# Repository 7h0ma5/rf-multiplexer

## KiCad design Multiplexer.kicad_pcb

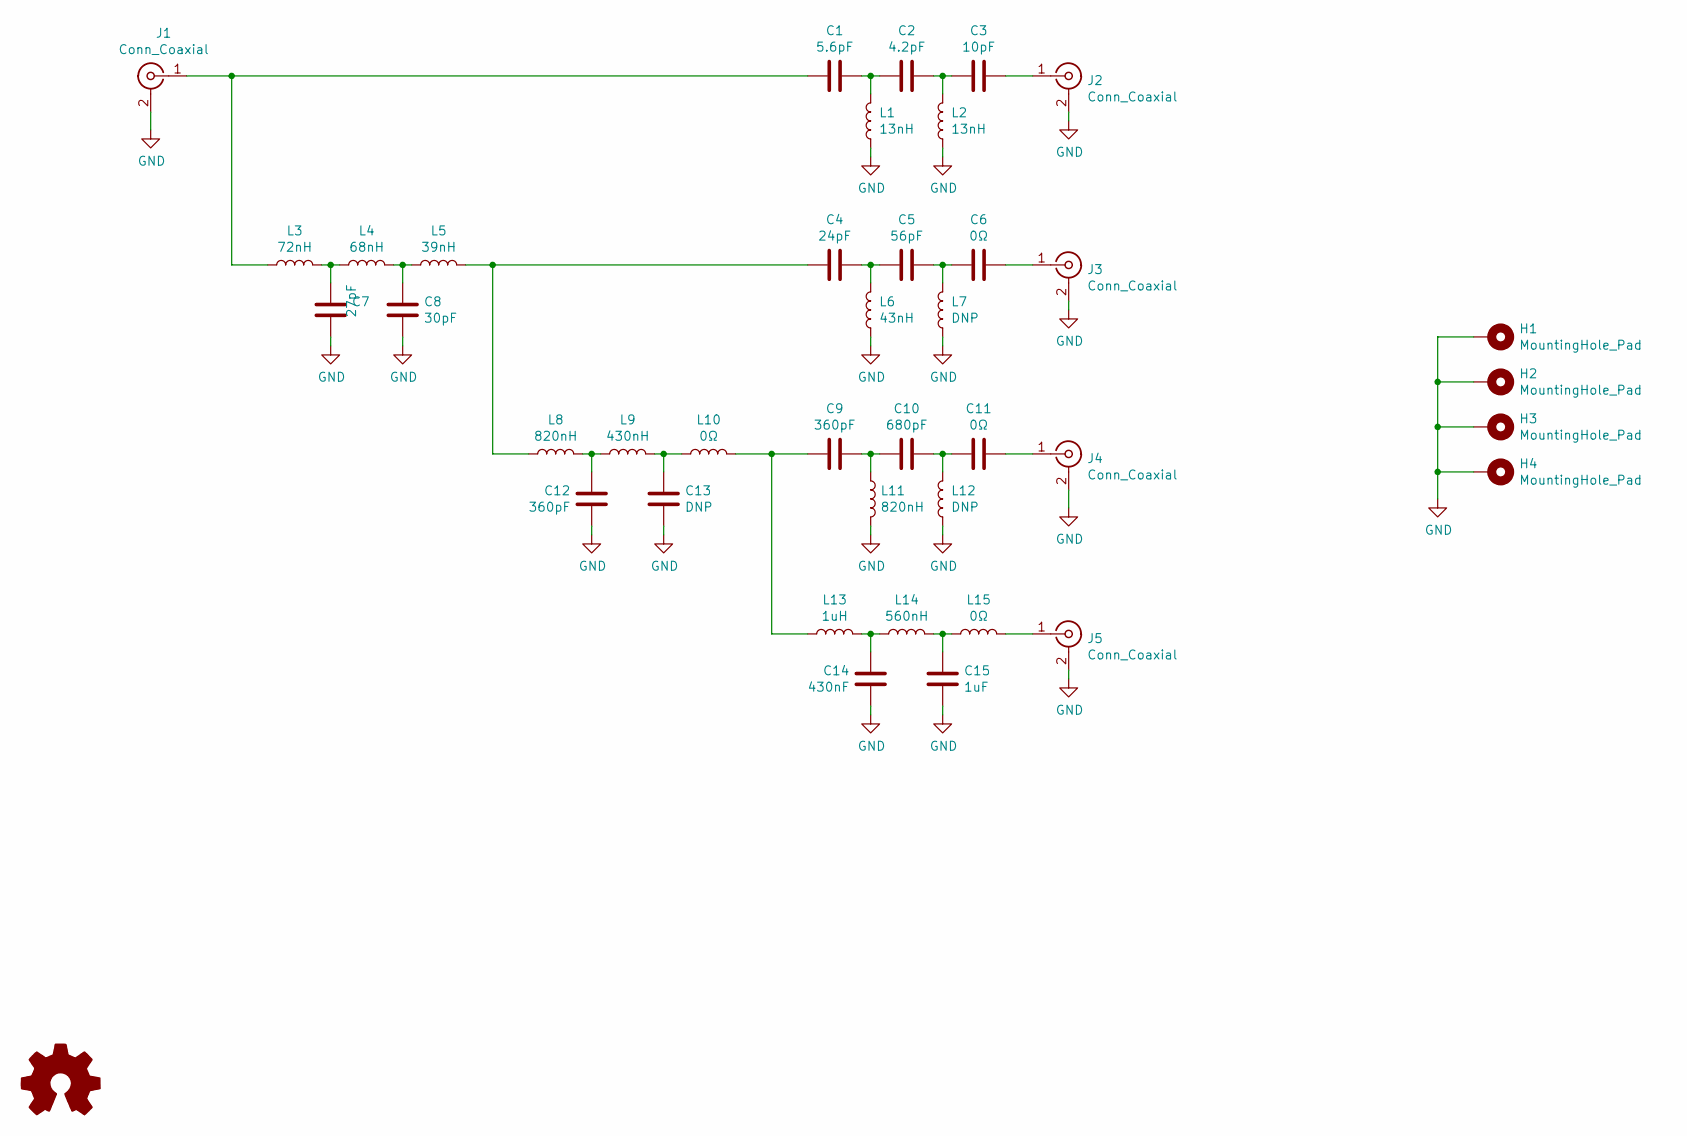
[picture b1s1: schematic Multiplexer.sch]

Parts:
C1: 5.6pF; C_0402_1005Metric; MPN GJM1555C1H5R6BB01
C2: 4.2pF; C_0402_1005Metric; MPN GJM1555C1H4R2BB01
C3: 10pF; C_0402_1005Metric; MPN GJM1555C1H100FB01
C4: 24pF; C_0402_1005Metric; MPN GJM1555C1H240FB01
C5: 56pF; C_0402_1005Metric; MPN GQM1885C1H560GB01
C6, C11: 0Ω; C_0402_1005Metric
C7: 27pF; C_0402_1005Metric; MPN GJM1555C1H270FB01
C8: 30pF; C_0402_1005Metric; MPN GJM1555C1H300FB01
C9: 360pF; C_0402_1005Metric
C10: 680pF; C_0402_1005Metric
C12: 360pF; C_0402_1005Metric; MPN GRM1555C1H361JA01
C13: DNP; C_0402_1005Metric
C14: 430nF; C_0603_1608Metric
C15: 1uF; C_0603_1608Metric
H1, H2, H3, H4: MountingHole_Pad; MountingHole_3.2mm_M3_Pad
J1, J2, J3, J4, J5: Conn_Coaxial; SMA_Connector
L1, L2: 13nH; L_0402_1005Metric; MPN LQW15AN13NG00
L3: 72nH; L_0402_1005Metric; MPN LQW15AN72NG00
L4: 68nH; L_0402_1005Metric; MPN LQW15AN68NG00
L5: 39nH; L_0402_1005Metric; MPN LQW15AN39NG00
L6: 43nH; L_0402_1005Metric; MPN LQW15AN43NG00
L7, L12: DNP; L_0402_1005Metric
L8, L11: 820nH; L_0402_1005Metric; MPN LQW15CNR82M10
L9: 430nH; L_0402_1005Metric; MPN LQW15CAR43J00
L10: 0Ω; L_0402_1005Metric
L13: 1uH; L_0402_1005Metric; MPN LQW15CA1R0K00
L14: 560nH; L_0402_1005Metric; MPN LQW15CAR56J00
L15: 0Ω; L_0603_1608Metric; MPN LQW15CAR56J00

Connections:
GND: C7.1, C8.1, C12.1, C13.1, C14.1, C15.1, H1.1, H2.1, H3.1, H4.1, J1.2 (Ext), J2.2 (Ext), J3.2 (Ext), J4.2 (Ext), J5.2 (Ext), L1.1, L2.1, L6.1, L7.1, L11.2, L12.1
unnamed: C1.1, C2.2, L1.2
unnamed: C1.2, J1.1 (In), L3.1
unnamed: C2.1, C3.2, L2.2
unnamed: C3.1, J2.1 (In)
unnamed: C4.1, C5.2, L6.2
unnamed: C4.2, L5.2, L8.1
unnamed: C5.1, C6.2, L7.2
unnamed: C6.1, J3.1 (In)
unnamed: C7.2, L3.2, L4.1
unnamed: C8.2, L4.2, L5.1
unnamed: C9.2, L10.2, L13.1
unnamed: C10.1, C11.2, L12.2
unnamed: C9.1, C10.2, L11.1
unnamed: C11.1, J4.1 (In)
unnamed: C12.2, L8.2, L9.1
unnamed: C13.2, L9.2, L10.1
unnamed: C14.2, L13.2, L14.1
unnamed: C15.2, L14.2, L15.1
unnamed: J5.1 (In), L15.2

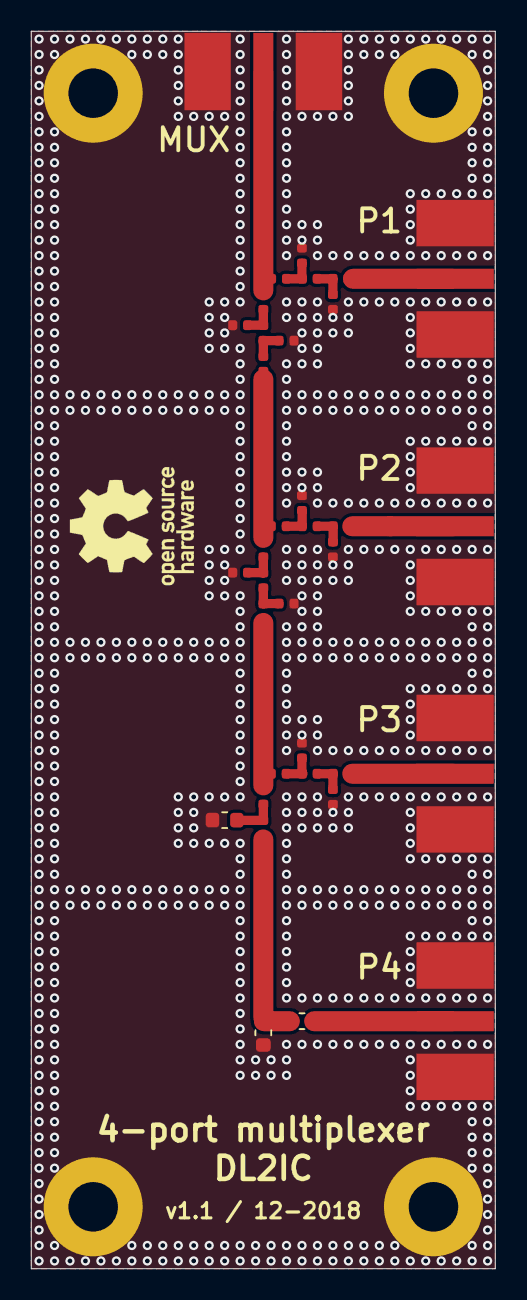
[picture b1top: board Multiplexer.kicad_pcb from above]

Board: 2 copper layers, 30.0 x 80.0 mm, 39 parts (0 on the bottom side), 20 nets.

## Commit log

2018-12-24 Update PCB logos
